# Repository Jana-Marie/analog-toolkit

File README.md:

# permanently moved to [codeberg/analog-toolkit](https://codeberg.org/analog-toolkit)

# analog-toolkit
A small and simple STM32G431 based dev board, doubling as a simple analog-to-USB acquisition tool.

Next to 6 single ended or 2 differential ADC inputs, there are 3 PGA connected ADC channels, 3 general purpose IO, 2 DAC outputs, 2 Timer outputs, and several protocols such as UART, I2C, USB FS and USB-PD. All ADCs have a standard input resolution of 12 bits, with hardware oversampling up to 16 bits, the DAC has 12 bits resolution. 
Equiped with a DFU bootloader, this board can simply be flashed from USB. All Ports are available through standard 2.54mm pinheader, a scope aligator clip can be attached to the grounding tab. A RGB led allows for direct status indication.

<table>
  <tbody>
    <tr>
      <td>
        
      </td>
      <td>
        
      </td>
    </tr>
    <tr>
      <td colspan="2">
        
      </td>
    </tr>
  </tbody>
</table>

## folder structure
```
 /hardware          - PCB files
 /ADC               - ADC sampling firmware, with selectable samplerate and API
 /ADC/software      - python receiving sketch for ADC firmware
 /DAC/              - DAC firmware bit, this one doesn't do much yet
 /pd-dev/           - USB-PD Sink firmware
```

## things I want to do and explore

#### HW

 - [x] replace RGB led with two discrete LEDs
 - [x] cheaper JLC version, keep functionality
 
#### SW/FW

 - [ ] build CLI
   - [ ] build basic CLI firmware
 - [ ] improve ADC fw
   - [ ] add interactive python console (60% done)
   - [ ] PGA current and temperature sensing
   - [ ] Implement byte stuffing
 - [ ] improve DAC fw
   - [ ] make sample rate settable
   - [ ] make sample settable
 - [ ] Implement Sigrok protocol
 - [ ] Implement SCPI
 - [x] USB-PD firmware
 
## license
 
Copyright Jana Marie Hemsing 2026.

This source describes Open Hardware and is licensed under the CERN-OHL-S v2.

You may redistribute and modify this source and make products using it under the terms of the CERN-OHL-S v2 (https://ohwr.org/cern_ohl_s_v2.txt).

This source is distributed WITHOUT ANY EXPRESS OR IMPLIED WARRANTY, INCLUDING OF MERCHANTABILITY, SATISFACTORY QUALITY AND FITNESS FOR A PARTICULAR PURPOSE. Please see the CERN-OHL-S v2 for applicable conditions.

Source location: https://github.com/Jana-Marie/analog-toolkit

As per CERN-OHL-S v2 section 4, should You produce hardware based on this source, You must where practicable maintain the Source Location visible on the external case of the Gizmo or other products you make using this source.

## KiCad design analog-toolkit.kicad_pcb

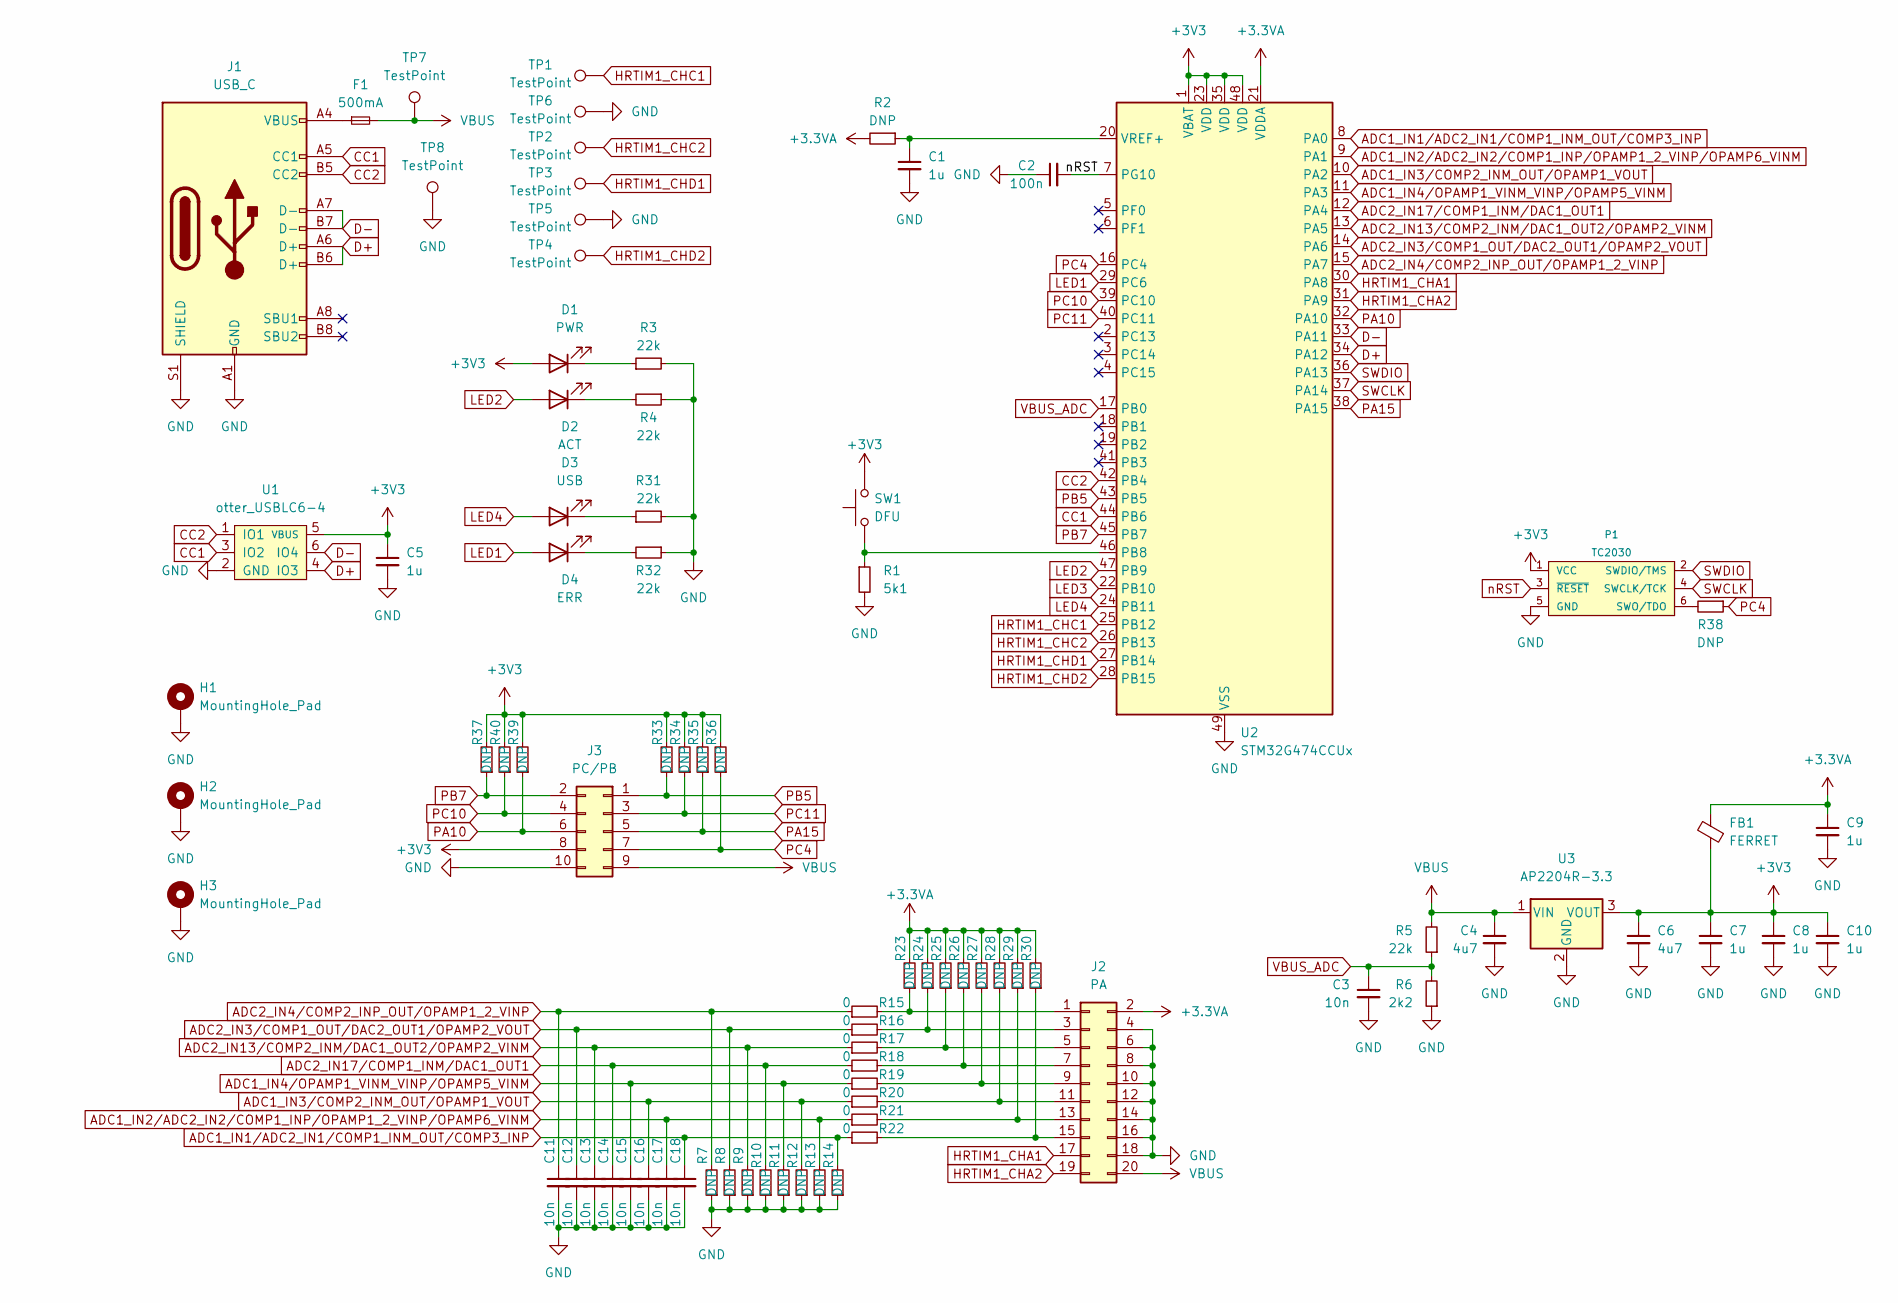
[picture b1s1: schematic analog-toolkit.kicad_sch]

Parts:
C1, C5, C7, C8, C9, C10: 1u; C_0402; lcsc C52923
C2: 100n; C_0402
C3, C11, C12, C13, C14, C15, C16, C17, C18: 10n; C_0402; lcsc C15195
C4, C6: 4u7; C_0805; lcsc C1779
D1: PWR; LED_0805_2012Metric
D2: ACT; LED_0805_2012Metric
D3: USB; LED_0805_2012Metric
D4: ERR; LED_0805_2012Metric
F1: 500mA; R_0805
FB1: FERRET; R_0603; lcsc C1002
H1, H2, H3: MountingHole_Pad; MountingHole_2.2mm_M2_ISO7380_Pad
J1: USB_C; USB-C 16Pin
J2: PA; IDC-Header_2x10_P2.54mm_Horizontal
J3: PC/PB; IDC-Header_2x05_P2.54mm_Horizontal
P1: TC2030
R1: 5k1; R_0402
R2, R7, R8, R9, R10, R11, R12, R13, R14, R23, R24, R25, R26, R27, R28, R29, R30, R33, R34, R35, R36, R37, R38, R39, R40: DNP; R_0402
R3, R4, R31, R32: 22k; R_0402
R5: 22k; R_0402; lcsc C25768
R6: 2k2; R_0402; lcsc C25890
R15, R16, R17, R18, R19, R20, R21, R22: 0; R_0402; lcsc C17168
SW1: DFU; SW_SPST_PTS810
TP1, TP2, TP3, TP4, TP5, TP6, TP7, TP8: TestPoint; TestPoint_Pad_1.0x1.0mm
U1: otter_USBLC6-4; SOT-23-6
U2: STM32G474CCUx; QFN-48-1EP_7x7mm_P0.5mm_EP5.6x5.6mm
U3: AP2204R-3.3; SOT-89-3

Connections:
+3.3VA: C9.1, FB1.2, J2.2, R2.2, R23.2, R24.2, R25.2, R26.2, R27.2, R28.2, R29.2, R30.2, U2.21 (VDDA)
+3V3: C5.1, C6.1, C7.1, C8.1, C10.1, D1.2 (A), FB1.1, J3.8, P1.1 (VCC), R33.2, R34.2, R35.2, R36.2, R37.2, R39.2, R40.2, SW1.2, U1.5 (VBUS), U2.1 (VBAT), U2.23 (VDD), U2.35 (VDD), U2.48 (VDD), U3.3 (VOUT)
ADC1_IN1/ADC2_IN1/COMP1_INM_OUT/COMP3_INP: C18.1, R14.2, R22.1, U2.8 (PA0)
ADC1_IN2/ADC2_IN2/COMP1_INP/OPAMP1_2_VINP/OPAMP6_VINM: C17.1, R13.2, R21.1, U2.9 (PA1)
ADC1_IN3/COMP2_INM_OUT/OPAMP1_VOUT: C16.1, R12.2, R20.1, U2.10 (PA2)
ADC1_IN4/OPAMP1_VINM_VINP/OPAMP5_VINM: C15.1, R11.2, R19.1, U2.11 (PA3)
ADC2_IN3/COMP1_OUT/DAC2_OUT1/OPAMP2_VOUT: C12.1, R8.2, R16.1, U2.14 (PA6)
ADC2_IN4/COMP2_INP_OUT/OPAMP1_2_VINP: C11.1, R7.2, R15.1, U2.15 (PA7)
ADC2_IN13/COMP2_INM/DAC1_OUT2/OPAMP2_VINM: C13.1, R9.2, R17.1, U2.13 (PA5)
ADC2_IN17/COMP1_INM/DAC1_OUT1: C14.1, R10.2, R18.1, U2.12 (PA4)
CC1: J1.A5 (CC1), U1.3 (IO2), U2.44 (PB6)
CC2: J1.B5 (CC2), U1.1 (IO1), U2.42 (PB4)
D+: J1.A6 (D+), J1.B6 (D+), U1.4 (IO3), U2.34 (PA12)
D-: J1.A7 (D-), J1.B7 (D-), U1.6 (IO4), U2.33 (PA11)
GND: C1.2, C2.1, C3.2, C4.2, C5.2, C6.2, C7.2, C8.2, C9.2, C10.2, C11.2, C12.2, C13.2, C14.2, C15.2, C16.2, C17.2, C18.2, H1.1, H2.1, H3.1, J1.A1 (GND), J1.A12 (GND), J1.B1 (GND), J1.B12 (GND), J1.S1 (SHIELD), J2.4, J2.6, J2.8, J2.10, J2.12, J2.14, J2.16, J2.18, J3.10, P1.5 (GND), R1.2, R3.2, R4.1, R6.1, R7.1, R8.1, R9.1, R10.1, R11.1, R12.1, R13.1, R14.1, R31.2, R32.1, TP5.1, TP6.1, TP8.1, U1.2 (GND), U2.49 (VSS), U3.2 (GND)
HRTIM1_CHA1: J2.17, U2.30 (PA8)
HRTIM1_CHA2: J2.19, U2.31 (PA9)
HRTIM1_CHC1: TP1.1, U2.25 (PB12)
HRTIM1_CHC2: TP2.1, U2.26 (PB13)
HRTIM1_CHD1: TP3.1, U2.27 (PB14)
HRTIM1_CHD2: TP4.1, U2.28 (PB15)
LED1: D4.2 (A), U2.29 (PC6)
LED2: D2.2 (A), U2.47 (PB9)
LED3: U2.22 (PB10)
LED4: D3.2 (A), U2.24 (PB11)
unnamed: D1.1 (K), R3.1
unnamed: D2.1 (K), R4.2
unnamed: D3.1 (K), R31.1
unnamed: D4.1 (K), R32.2
unnamed: F1.1, J1.A4 (VBUS), J1.A9 (VBUS), J1.B4 (VBUS), J1.B9 (VBUS)
unnamed: J2.1, R15.2, R23.1
unnamed: J2.3, R16.2, R24.1
unnamed: J2.5, R17.2, R25.1
unnamed: J2.7, R18.2, R26.1
unnamed: J2.9, R19.2, R27.1
unnamed: J2.11, R20.2, R28.1
unnamed: J2.13, R21.2, R29.1
unnamed: J2.15, R22.2, R30.1
unnamed: P1.6 (SWO/TDO), R38.2
unnamed: R1.1, SW1.1, U2.46 (PB8)
unnamed: C1.1, R2.1, U2.20 (VREF+)
PA10: J3.6, R39.1, U2.32 (PA10)
PA15: J3.5, R35.1, U2.38 (PA15)
PB5: J3.1, R33.1, U2.43 (PB5)
PB7: J3.2, R37.1, U2.45 (PB7)
PC4: J3.7, R36.1, R38.1, U2.16 (PC4)
PC10: J3.4, R40.1, U2.39 (PC10)
PC11: J3.3, R34.1, U2.40 (PC11)
SWCLK: P1.4 (SWCLK/TCK), U2.37 (PA14)
SWDIO: P1.2 (SWDIO/TMS), U2.36 (PA13)
VBUS: C4.1, F1.2, J2.20, J3.9, R5.2, TP7.1, U3.1 (VIN)
VBUS_ADC: C3.1, R5.1, R6.2, U2.17 (PB0)
nRST: C2.2, P1.3 (~RESET), U2.7 (PG10)

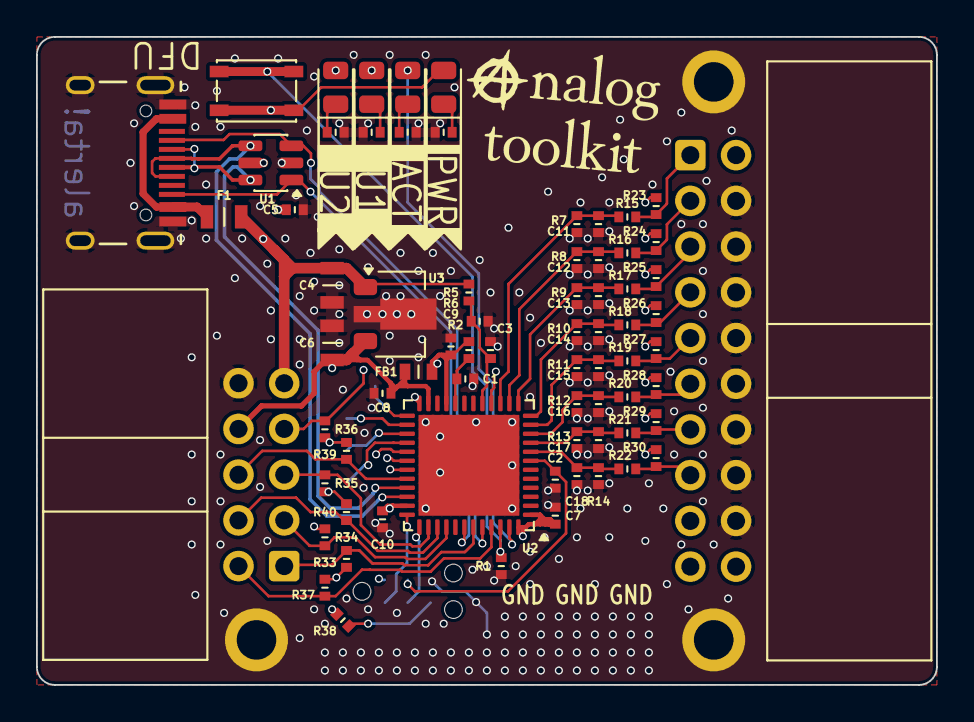
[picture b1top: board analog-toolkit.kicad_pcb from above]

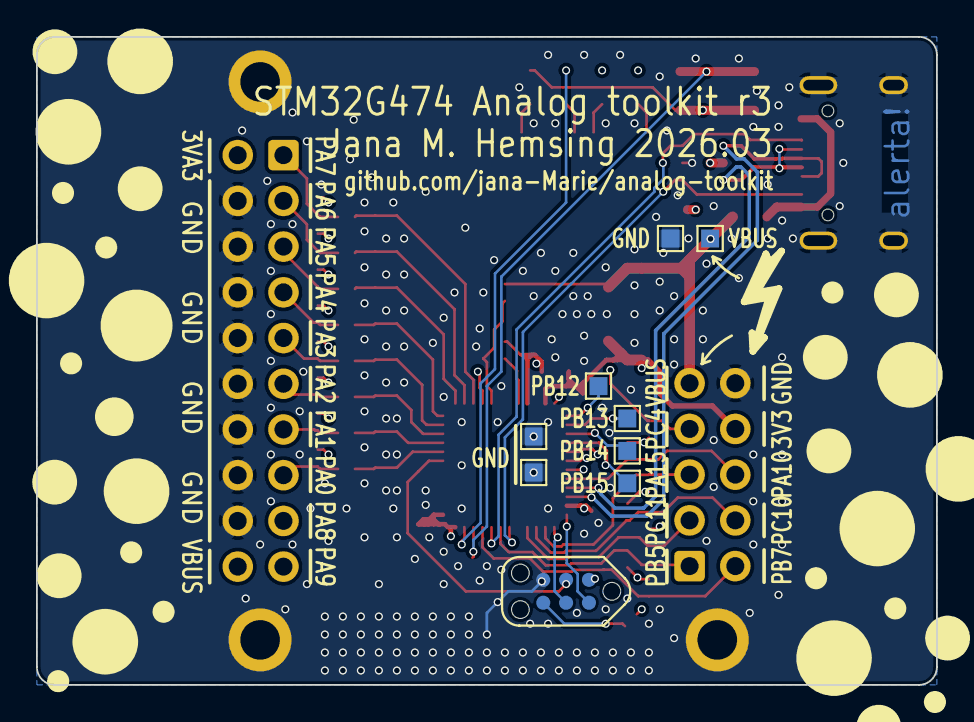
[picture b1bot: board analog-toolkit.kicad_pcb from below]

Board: 4 copper layers, 50.0 x 36.0 mm, 83 parts (9 on the bottom side), 52 nets.

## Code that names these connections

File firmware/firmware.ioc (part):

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Mcu.Name=STM32G431K(6-8-B)Tx
Mcu.Package=LQFP32
Mcu.UserName=STM32G431K8Tx
PA0.Mode=IN1-Single-Ended
PA0.Signal=ADC1_IN1
PA1.Mode=PGA_Internally_Connected
PA1.Signal=OPAMP1_VINP
PA10.Mode=Asynchronous
PA10.Signal=USART1_RX
PA11.Mode=Device
PA11.Signal=USB_DM
PA12.Mode=Device
PA12.Signal=USB_DP
PA13.Mode=Serial_Wire
PA13.Signal=SYS_JTMS-SWDIO
PA14.Mode=Serial_Wire
PA14.Signal=SYS_JTCK-SWCLK
PA15.Mode=I2C
PA15.Signal=I2C1_SCL
PA2.Mode=IN3-Differential
PA2.Signal=ADC1_IN3
PA3.Mode=IN3-Differential
PA3.Signal=ADC1_IN4
PA4.Mode=IN17-Single-Ended
PA4.Signal=ADC2_IN17
PA5.Mode=IN13-Single-Ended
PA5.Signal=ADC2_IN13
PA6.Mode=IN3-Single-Ended
PA6.Signal=ADC2_IN3
PA7.Mode=PGA_Internally_Connected
PA7.Signal=OPAMP2_VINP
PA9.Mode=Asynchronous
PA9.Signal=USART1_TX
PB0.Mode=Follower_Internally_Connected
PB0.Signal=OPAMP3_VINP
PB3.Signal=S_TIM2_CH2
PB4.Mode=Sink_AllSignals
PB4.Signal=UCPD1_CC2
PB5.Signal=S_TIM3_CH2
PB6.Mode=Sink_AllSignals
PB6.Signal=UCPD1_CC1
PB7.Mode=I2C
PB7.Signal=I2C1_SDA
PB8-BOOT0.Signal=GPIO_Input
PF0-OSC_IN.Signal=GPIO_Output
PF1-OSC_OUT.Signal=GPIO_Output
RCC.HSE_VALUE=8000000
RCC.SYSCLKFreq_VALUE=96000000
RCC.SYSCLKSource=RCC_SYSCLKSOURCE_PLLCLK
board=custom

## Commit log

2023-05-10 added kicad files
2023-05-10 added all files
2023-05-10 added images
2023-07-02 added fw
2023-07-25 updated images
2023-07-25 moved FW
2023-07-25 added DAC fw
2023-07-25 updated kicad files
2023-07-25 added drv5055 tesla probe code
2023-09-22 updated sw
2024-07-06 updated gitignore
2024-07-06 added pd-dev fw
2024-07-06 removed ozone files
2024-07-06 added more todos ._.
2026-01-23 updated version
2026-01-23 added shutter speed sensor
2026-02-06 bumped improved version
2026-02-16 removed drc
2026-02-16 updated BOM files for JLC
2026-02-16 updated boards, replaced RGB led
2026-02-18 ammended readme
2026-02-18 updated board with jlc-specific parts
2026-02-18 added jlc bom and pos
2026-02-18 rm old files
2026-03-14 added r3
2026-03-14 added lid for r3
